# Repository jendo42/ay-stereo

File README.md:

# ZX Spectrum AY Stereo
This is *yet another* but opensource design of the ACB/ABC stereo enhancement for ZX Spectrum computers. Original electrical design by Ben Versteeg / [ByteDelight.com](https://www.bytedelight.com).

There are multiple variants of the wiring in the [docs](docs/) directory but the original installation manual from ByteDelight v2014 can be found [here](docs/bd-v2014-manual.pdf).

Added option to solder the additional resistors for +2/+3 models directly on board.

## Latest version
 - gerber data generated for JLCPCB are [here](r1/gerber/)
 - schematic for *r1* is [here](r1/ay-stereo-sch.pdf)

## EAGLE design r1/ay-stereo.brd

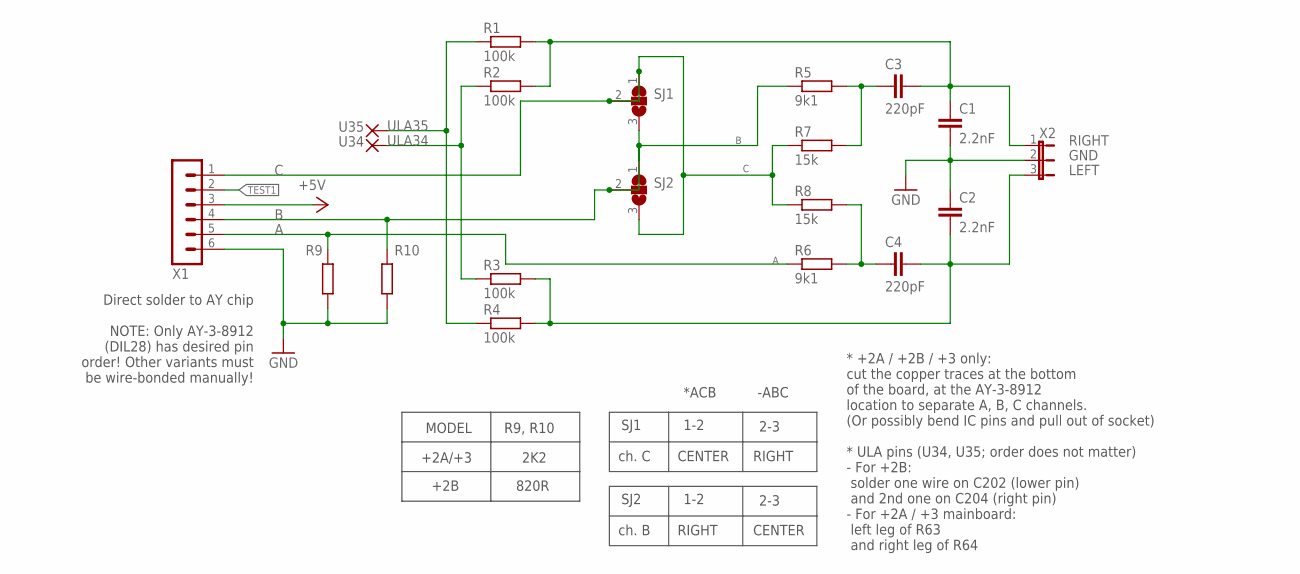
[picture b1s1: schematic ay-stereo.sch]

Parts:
C1, C2: 2.2nF; C0805
C3, C4: 220pF; C0805
R1, R2, R3, R4: 100k; R0805
R5, R6: 9k1; R0805
R7, R8: 15k; R0805
R9, R10: R-EU_R0805; R0805
SJ1, SJ2: SJ2W; SJ_2
U34, U35: 1,6/0,8
X1: MA06-1
X2: JP2E; JP2

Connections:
+5V: X1.3
A: R6.1, R9.2, X1.5
B: R5.1, R10.2, SJ1.3, SJ2.1, SJ2.2, X1.4
C: R7.1, R8.1, SJ1.1, SJ1.2, SJ2.3, X1.1
GND: C1.2, C2.1, R9.1, R10.1, X1.6, X2.2
LEFT: C2.2, C4.2, R3.2, R4.2, X2.3
unnamed: C3.1, R5.2, R7.2
unnamed: C4.1, R6.2, R8.2
RIGHT: C1.1, C3.2, R1.2, R2.2, X2.1
TEST1: X1.2
ULA34: R2.1, R3.1, U34.1
ULA35: R1.1, R4.1, U35.1

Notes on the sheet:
SJ1
1-2
2-3
ch. C
CENTER
RIGHT
SJ2
ch. B
+2B
+2A/+3
R9, R10
820R
2K2
MODEL
* +2A / +2B / +3 only: cut the copper traces at the bottom of the board, at the AY-3-8912 location to separate A, B, C channels. (Or possibly bend IC pins and pull out of socket) * ULA pins (U34, U35; order does not matter) - For +2B: solder one wire on C202 (lower pin) and 2nd one on C204 (right p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
*ACB
-ABC
Direct solder to AY chip NOTE: Only AY-3-8912 (DIL28) has desired pin order! Other variants must be wire-bonded manually!

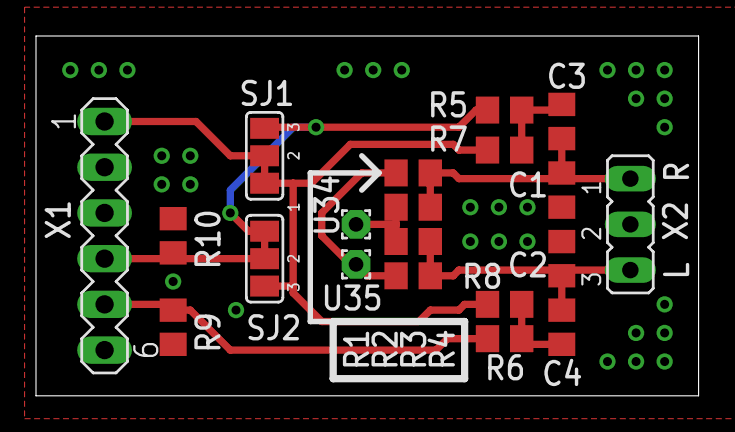
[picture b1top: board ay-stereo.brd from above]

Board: 2 copper layers, 36.8 x 20.0 mm, 20 parts (0 on the bottom side), 10 nets.
